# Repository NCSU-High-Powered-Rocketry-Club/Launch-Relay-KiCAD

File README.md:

# Launch Relay KiCad
This project contains the KiCad files for HPRC's Launch Relay board. This PCB was designed for the club's rover payload, which will be flown in the 2027 IREC competition.

## Description
The Launch Relay is designed to help conserve battery life and processing power of the rover payload by acting as a very low-power isolated solid-state relay. The board features an STM32 microcontroller, onboard flash for logging data, and an accelerometer to detect when the rocket launches and lands. It is all powered from a standard coin cell battery.

The firmware for the STM32 can be found [here](https://github.com/NCSU-High-Powered-Rocketry-Club/GildedTrigger).

## Component Overview
Here are the main components that the board uses:

| Component Type | Part Number | Datasheet |
|---|---|---|
| Microcontroller | STM32U083KCU6 | [STMicroelectronics](https://www.st.com/resource/en/datasheet/stm32u083kc.pdf) |
| Accelerometer | BMA580 | [Bosch Sensortec](https://www.bosch-sensortec.com/media/boschsensortec/downloads/datasheets/bst-bma580-ds000.pdf) |
| SPI NOR Flash (32 Mbit) | MX25R3235FM1IL0 | [Macronix](https://www.macronix.com/Lists/Datasheet/Attachments/8755/MX25R3235F%2C%20Wide%20Range%2C%2032Mb%2C%20v1.8.pdf) |
| D-Type Flip-Flop | SN74LVC1G74DQER | [Texas Instruments](https://www.ti.com/lit/ds/symlink/sn74lvc1g74.pdf) |
| N-Channel Power MOSFET | NVMFS5C460NLAFT1G-YE | [onsemi](https://www.onsemi.com/pdf/datasheet/nvmfs5c460nl-d.pdf) |

The STM32 was chosen for it's lower power consumption and small footprint, while still offering the needed peripherals for the board. The BMA580 accelerometer has excellent programmable interrupt features, allowing for customizable acceleration slopes and durations to be used to detect launch and wake the STM32. After launch, the acceleration data is stored to the MX25R3235F flash, which can be later retrieved for post-processing using the UART and DUMP pin provided on the pin header.

The board has two independent solid-state relays and are controlled using optocouplers. Optocouplers have relatively high power consumption compared to the rest of the board so a flip-flop circuit is used to limit the duration the optocoupler is powered. This powers the gate of the power MOSFET, which is wired as a low-side switch for the external circuit. Both relays on the board are designed for loads up to 10A. External circits must be at least 5.1V.

## Libraries
Some of the KiCad symbols and footprints for this project are not included in the standard KiCad library, and are located in [HPRC's KiCad Library](https://github.com/NCSU-High-Powered-Rocketry-Club/HPRC-KiCad-Library)

## PCBWay
A special thank you to our sponsor, [PCBWay](https://www.pcbway.com/), for supporting the manufacturing of this custom PCB! As a competitive high-powered rocketry team, reliable electronics are essential to the success of our projects. PCBWay's high-quality PCB manufacturing services have helped us turn our designs into functional hardware, allowing us to develop and test custom electronics for our rockets and payloads. Their support, attention to detail, and excellent communication throughout the manufacturing process have been greatly appreciated. We are grateful for their contribution to our team's success and highly recommend checking out their services for your next electronics project!

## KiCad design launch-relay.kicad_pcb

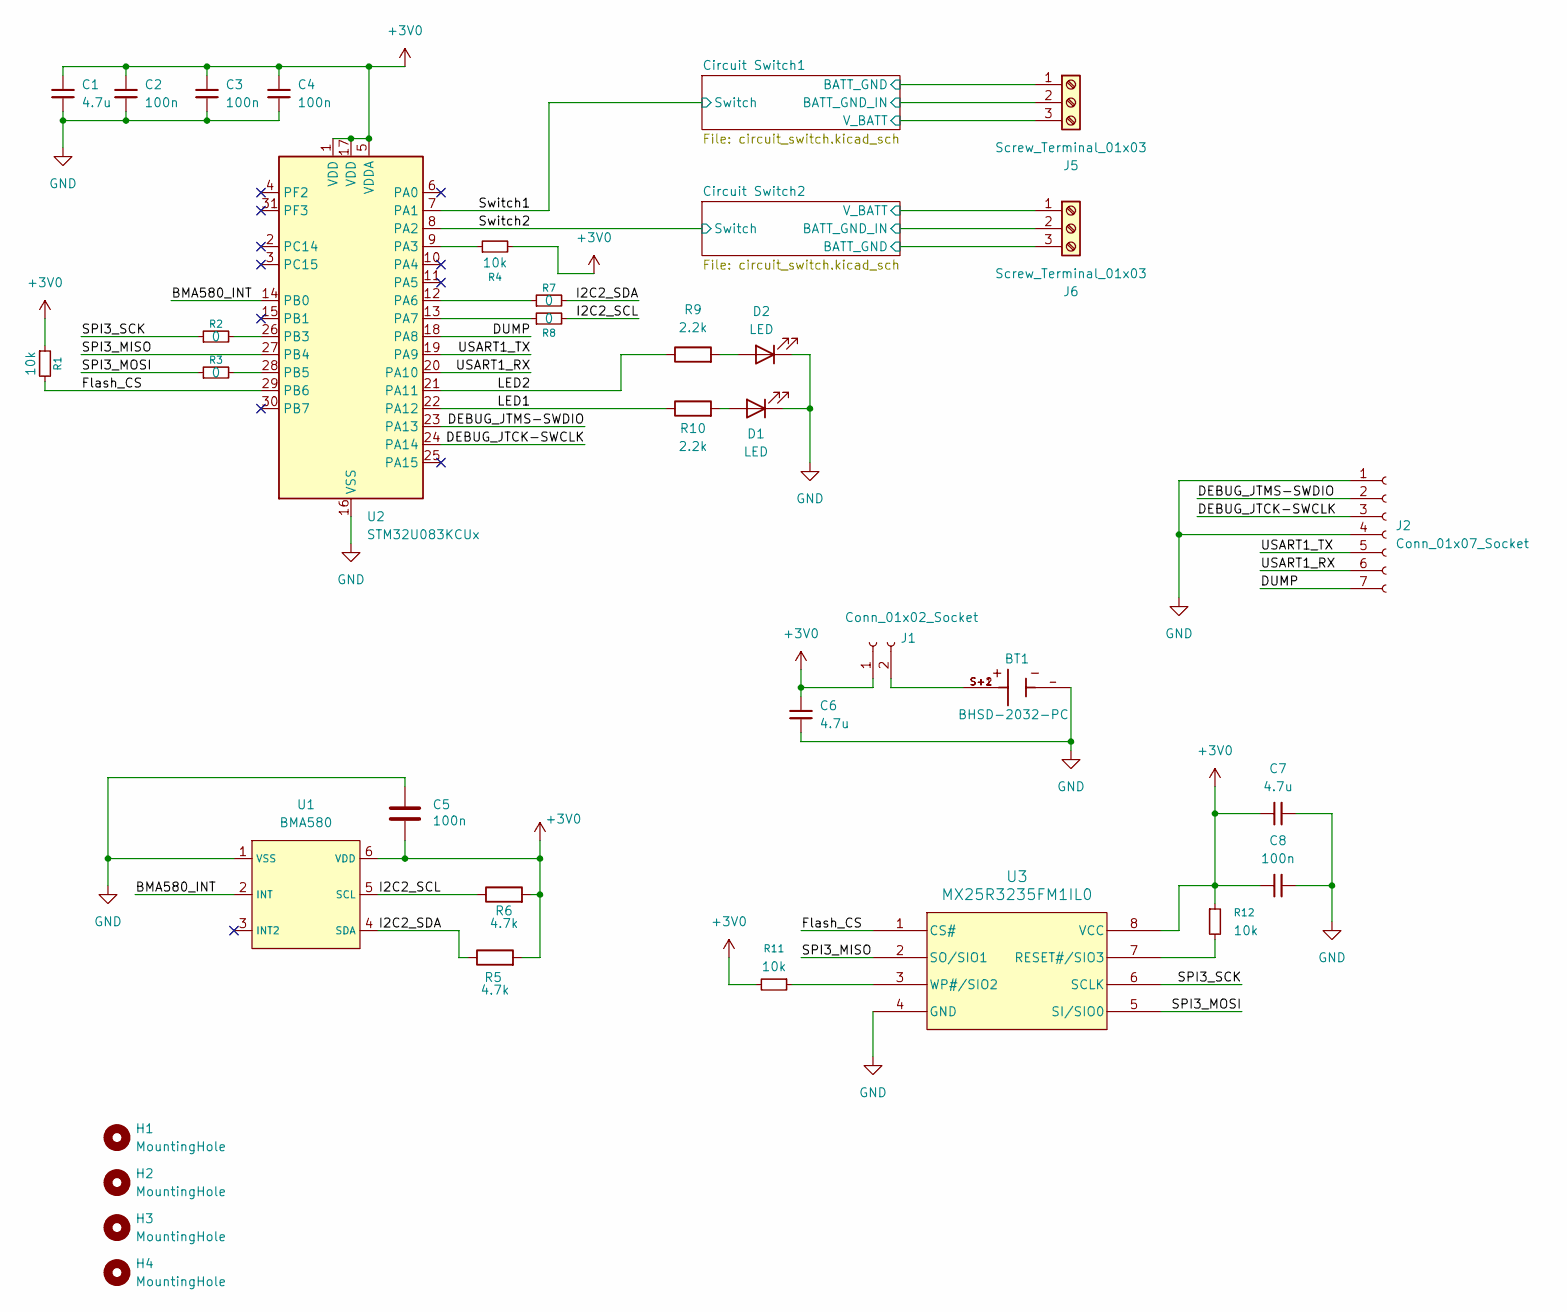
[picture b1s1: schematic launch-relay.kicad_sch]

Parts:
BT1: BHSD-2032-PC; BAT_BHSD-2032-PC; PARTREV K
C1, C6, C7: 4.7u; C_0402_1005Metric; Manufacturer_Part_Number GRM155R60J475ME47D
C2, C3, C4, C5, C8: 100n; C_0402_1005Metric; Manufacturer_Part_Number GRM155R61A104KA01D
D1: LED; LED_0805_2012Metric; Manufacturer_Part_Number APT2012SURCK
D2: LED; LED_0805_2012Metric; Manufacturer_Part_Number APT2012CGCK
H1, H2, H3, H4: MountingHole; MountingHole_2.2mm_M2
J1: Conn_01x02_Socket; PinSocket_1x02_P2.54mm_Vertical
J2: Conn_01x07_Socket; PinSocket_1x07_P2.54mm_Vertical
J5, J6: Screw_Terminal_01x03; TerminalBlock_Philmore_TB133_1x03_P5.00mm_Horizontal
R1, R4, R11, R12: 10k; R_0402_1005Metric; Manufacturer_Part_Number RC0402FR-0710KL
R2, R3, R7, R8: 0; R_0402_1005Metric; Manufacturer_Part_Number RC0402FR-070RL
R5, R6: 4.7k; R_0402_1005Metric; Manufacturer_Part_Number RC0402FR-074k7L
R9, R10: 2.2k; R_0402_1005Metric; Manufacturer_Part_Number RC0402FR-072k2L
U1: BMA580; Manufacturer_Part_Number BMA580
U2: STM32U083KCUx; QFN-32-1EP_5x5mm_P0.5mm_EP3.45x3.45mm; Manufacturer_Part_Number STM32U083KCU6
U3: MX25R3235FM1IL0; SOP_8L_150_MAC; Manufacturer_Part_Number MX25R3235FM1IL0

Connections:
+3V0: C1.2, C2.2, C3.2, C4.2, C5.2, C6.2, C7.1, C8.1, J1.1, R1.1, R4.2, R5.2, R6.2, R11.2, R12.1, U1.6 (VDD), U2.1 (VDD), U2.5 (VDDA), U2.17 (VDD), U3.8 (VCC)
/BMA580_INT: U1.2 (INT), U2.14 (PB0)
/Circuit Switch1/BATT_GND: J5.1; also elsewhere on the board
/Circuit Switch1/BATT_GND_IN: J5.2; also elsewhere on the board
/Circuit Switch1/V_BATT: J5.3; also elsewhere on the board
/Circuit Switch2/BATT_GND: J6.3; also elsewhere on the board
/Circuit Switch2/BATT_GND_IN: J6.2; also elsewhere on the board
/Circuit Switch2/V_BATT: J6.1; also elsewhere on the board
/DEBUG_JTCK-SWCLK: J2.3, U2.24 (PA14)
/DEBUG_JTMS-SWDIO: J2.2, U2.23 (PA13)
/DUMP: J2.7, U2.18 (PA8)
/Flash_CS: R1.2, U2.29 (PB6), U3.1 (CS#)
/I2C2_SCL: R6.1, R8.2, U1.5 (SCL)
/I2C2_SDA: R5.1, R7.2, U1.4 (SDA)
/LED1: R10.1, U2.22 (PA12)
/LED2: R9.1, U2.21 (PA11)
/SPI3_MISO: U2.27 (PB4), U3.2 (SO/SIO1)
/SPI3_MOSI: R3.1, U3.5 (SI/SIO0)
/SPI3_SCK: R2.1, U3.6 (SCLK)
/Switch1: U2.7 (PA1); also elsewhere on the board
/Switch2: U2.8 (PA2); also elsewhere on the board
/USART1_RX: J2.6, U2.20 (PA10)
/USART1_TX: J2.5, U2.19 (PA9)
GND: BT1.-, C1.1, C2.1, C3.1, C4.1, C5.1, C6.1, C7.2, C8.2, D1.1 (K), D2.1 (K), J2.1, J2.4, U1.1 (VSS), U2.16 (VSS), U2.32 (VSS), U2.33 (VSS), U3.4 (GND); also elsewhere on the board
unnamed: D1.2 (A), R10.2
unnamed: D2.2 (A), R9.2
unnamed: BT1.S+1, BT1.S+2, J1.2
unnamed: R4.1, U2.9 (PA3)
unnamed: R7.1, U2.12 (PA6)
unnamed: R8.1, U2.13 (PA7)
unnamed: R2.2, U2.26 (PB3)
unnamed: R3.2, U2.28 (PB5)
unnamed: R12.2, U3.7 (RESET#/SIO3)
unnamed: R11.1, U3.3 (WP#/SIO2)

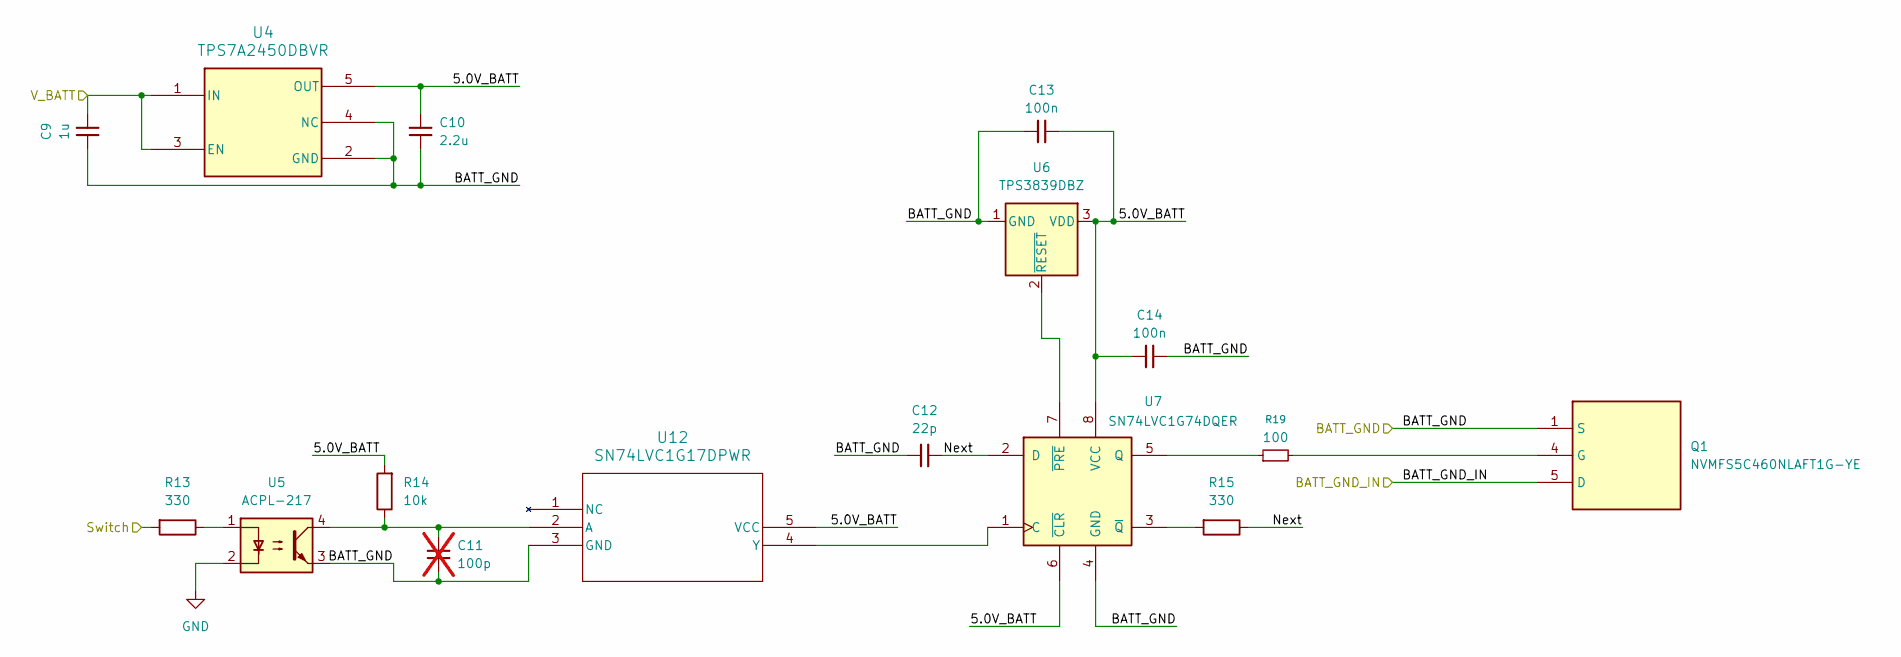
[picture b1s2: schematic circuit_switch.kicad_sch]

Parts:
C9: 1u; C_0402_1005Metric; Manufacturer_Part_Number GRM155R61E105MA12D
C10: 2.2u; C_0402_1005Metric; Manufacturer_Part_Number GRT155R61A225KE01D
C11: 100p; C_0402_1005Metric; not fitted
C12: 22p; C_0402_1005Metric; Manufacturer_Part_Number GRM1555C1H220JA01D
C13, C14: 100n; C_0402_1005Metric; Manufacturer_Part_Number GRM155R61A104KA01D
Q1: NVMFS5C460NLAFT1G-YE; NVMFS3D0P04M8LT1G; Manufacturer_Part_Number NVMFS5C460NLAFT1G-YE
R13, R15: 330; R_0402_1005Metric; Manufacturer_Part_Number RC0402FR-07330RL
R14: 10k; R_0402_1005Metric; Manufacturer_Part_Number RC0402FR-0710KL
R19: 100; R_0402_1005Metric; Manufacturer_Part_Number RC0402FR-07100RL
U4: TPS7A2450DBVR; SOT-23-5; Manufacturer_Part_Number TPS7A2450DBVR
U5: ACPL-217; SO-4_4.4x2.3mm_P1.27mm; Manufacturer_Part_Number ACPL-217-56CE
U6: TPS3839DBZ; SOT-23; Manufacturer_Part_Number TPS3839K50DBZR
U7: SN74LVC1G74DQER; X2SON-8_1.4x1mm_P0.35mm; Manufacturer_Part_Number SN74LVC1G74DQER
U12: SN74LVC1G17DPWR; Manufacturer_Part_Number SN74LVC1G17DPWR

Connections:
/Circuit Switch1/5.0V_BATT: C10.1, C13.1, C14.2, R14.2, U4.5 (OUT), U6.3 (VDD), U7.6 (~CLR), U7.8 (VCC), U12.5 (VCC)
/Circuit Switch1/BATT_GND: C9.1, C10.2, C11.1, C12.1, C13.2, C14.1, Q1.1 (S), Q1.2 (S), Q1.3 (S), U4.2 (GND), U4.4 (NC), U5.3, U6.1 (GND), U7.4 (GND), U12.3 (GND); also elsewhere on the board
/Circuit Switch1/BATT_GND_IN: Q1.5 (D), Q1.6 (D), Q1.7 (D), Q1.8 (D), Q1.9 (D); also elsewhere on the board
/Circuit Switch1/Next: C12.2, R15.1, U7.2 (D)
/Circuit Switch1/V_BATT: C9.2, U4.1 (IN), U4.3 (EN); also elsewhere on the board
/Switch1: R13.2; also elsewhere on the board
GND: U5.2; also elsewhere on the board
unnamed: Q1.4 (G), R19.2
unnamed: R13.1, U5.1
unnamed: U6.2 (~RESET), U7.7 (~PRE)
unnamed: R19.1, U7.5 (Q)
unnamed: R15.2, U7.3 (~Q)
unnamed: C11.2, R14.1, U5.4, U12.2 (A)
unnamed: U7.1 (C), U12.4 (Y)

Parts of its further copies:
C15: 1u; C_0402_1005Metric; Manufacturer_Part_Number GRM155R61E105MA12D
C16: 2.2u; C_0402_1005Metric; Manufacturer_Part_Number GRT155R61A225KE01D
C17: 100p; C_0402_1005Metric; not fitted
C18: 22p; C_0402_1005Metric; Manufacturer_Part_Number GRM1555C1H220JA01D
C19, C20: 100n; C_0402_1005Metric; Manufacturer_Part_Number GRM155R61A104KA01D
Q2: NVMFS5C460NLAFT1G-YE; NVMFS3D0P04M8LT1G; Manufacturer_Part_Number NVMFS5C460NLAFT1G-YE
R16, R18: 330; R_0402_1005Metric; Manufacturer_Part_Number RC0402FR-07330RL
R17: 10k; R_0402_1005Metric; Manufacturer_Part_Number RC0402FR-0710KL
R20: 100; R_0402_1005Metric; Manufacturer_Part_Number RC0402FR-07100RL
U8: TPS7A2450DBVR; SOT-23-5; Manufacturer_Part_Number TPS7A2450DBVR
U9: ACPL-217; SO-4_4.4x2.3mm_P1.27mm; Manufacturer_Part_Number ACPL-217-56CE
U10: TPS3839DBZ; SOT-23; Manufacturer_Part_Number TPS3839K50DBZR
U11: SN74LVC1G74DQER; X2SON-8_1.4x1mm_P0.35mm; Manufacturer_Part_Number SN74LVC1G74DQER
U13: SN74LVC1G17DPWR; Manufacturer_Part_Number SN74LVC1G17DPWR

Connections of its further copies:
/Circuit Switch2/5.0V_BATT: C16.1, C19.1, C20.2, R17.2, U8.5 (OUT), U10.3 (VDD), U11.6 (~CLR), U11.8 (VCC), U13.5 (VCC)
/Circuit Switch2/BATT_GND: C15.1, C16.2, C17.1, C18.1, C19.2, C20.1, Q2.1 (S), Q2.2 (S), Q2.3 (S), U8.2 (GND), U8.4 (NC), U9.3, U10.1 (GND), U11.4 (GND), U13.3 (GND); also elsewhere on the board
/Circuit Switch2/BATT_GND_IN: Q2.5 (D), Q2.6 (D), Q2.7 (D), Q2.8 (D), Q2.9 (D); also elsewhere on the board
/Circuit Switch2/Next: C18.2, R18.1, U11.2 (D)
/Circuit Switch2/V_BATT: C15.2, U8.1 (IN), U8.3 (EN); also elsewhere on the board
/Switch2: R16.2; also elsewhere on the board
GND: U9.2; also elsewhere on the board
unnamed: Q2.4 (G), R20.2
unnamed: R16.1, U9.1
unnamed: U10.2 (~RESET), U11.7 (~PRE)
unnamed: U11.1 (C), U13.4 (Y)
unnamed: R20.1, U11.5 (Q)
unnamed: R18.2, U11.3 (~Q)
unnamed: C17.2, R17.1, U9.4, U13.2 (A)

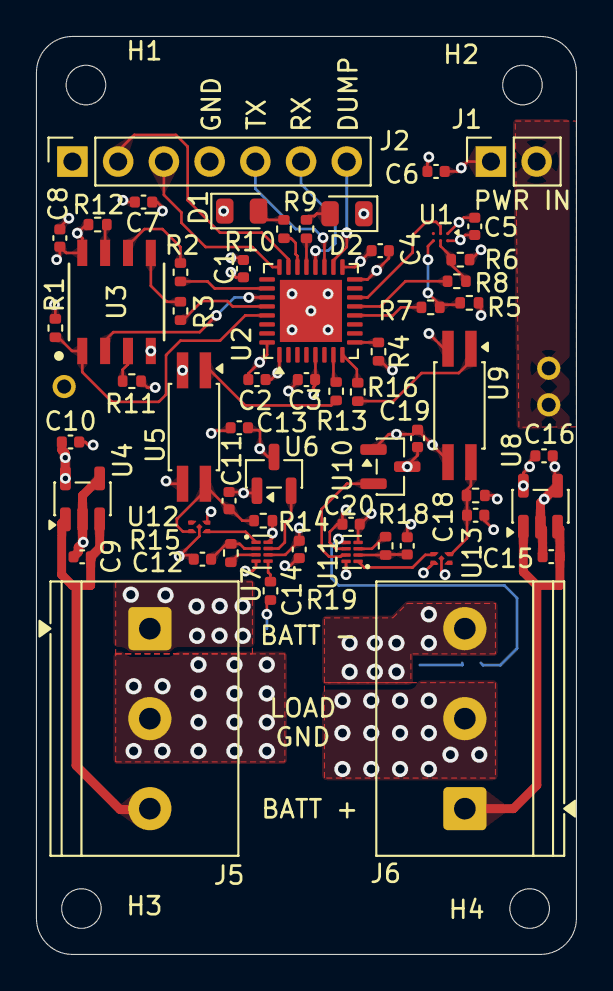
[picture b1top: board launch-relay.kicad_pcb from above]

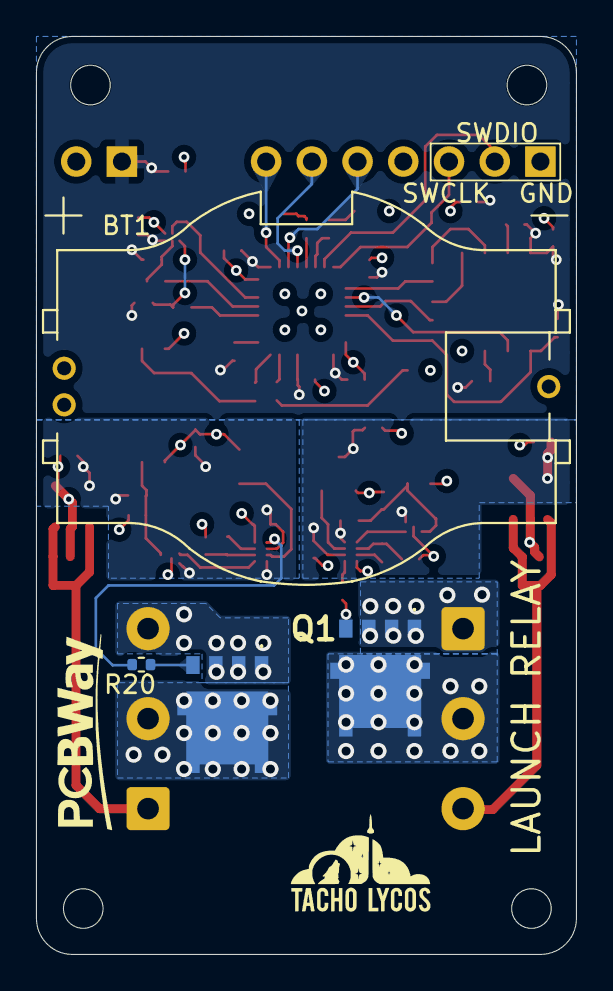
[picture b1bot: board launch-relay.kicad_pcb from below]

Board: 4 copper layers, 30.0 x 51.0 mm, 66 parts (4 on the bottom side), 52 nets.
